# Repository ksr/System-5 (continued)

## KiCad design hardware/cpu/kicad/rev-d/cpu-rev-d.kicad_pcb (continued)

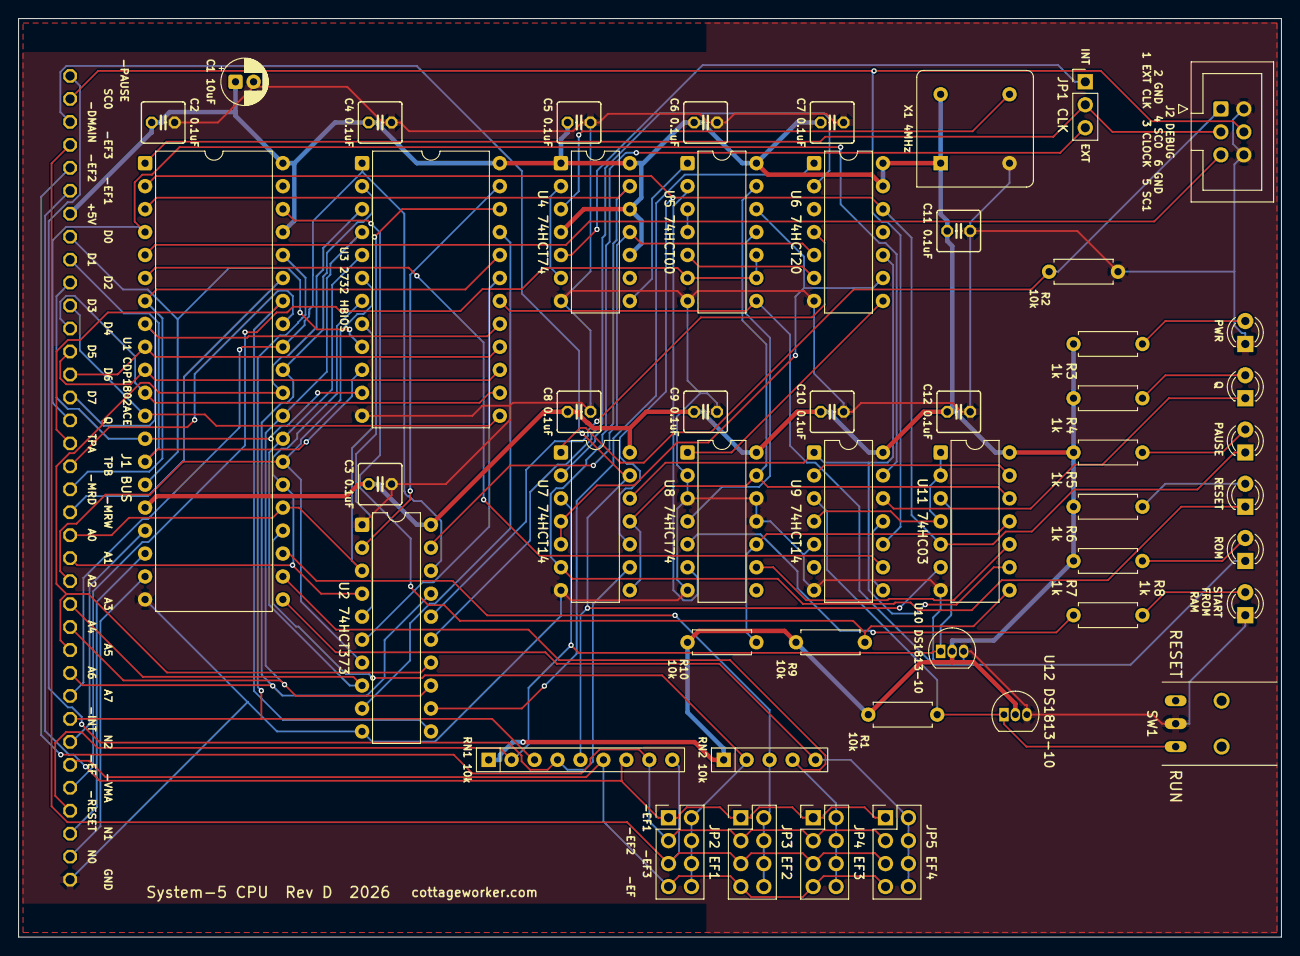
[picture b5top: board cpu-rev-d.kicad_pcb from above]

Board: 2 copper layers, 139.7 x 101.6 mm, 51 parts (0 on the bottom side), 83 nets.

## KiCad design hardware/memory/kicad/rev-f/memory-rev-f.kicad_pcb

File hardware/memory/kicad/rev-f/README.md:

# Memory Rev F (MEM3-F): KiCad master

> **Rev F (2026-11-18) is Rev E with EEPROM sockets and its silkscreen fixed.** Ken asked that morning for "the next
> version of memory card with fixed silkscreen", and that evening "yes put in Rev F but that isnt being ordered today"
> for the EEPROM sockets of `BACKLOG.md` (2026-10-30). Each EPROM socket takes a 27C256, as before, or a 28C256 EEPROM
> that the 1802 can rewrite in place. A jumper block per socket picks which (below).
>
> **Copper:** Rev E's, except where the sockets changed. 1,078 of Rev E's 1,084 track segments and vias are kept,
> identical and locked. The 6 that carried A14 through IC3's and IC5's pin 27 are gone. Freerouting added 74 segments
> and 1 via for the new connections, and a 75th, a 0.05 mm stitch inside one of Rev E's tracks (IC4's D6 net). Both planes,
> and every part but the four new ones, are where Rev E has them. Rev E (`../rev-e/README.md`) has been the card in
> the machine since 2026-10-31; its notes on building it (74HCT151 for all four muxes, the CD4050B buffers) apply to
> Rev F unchanged.
>
> **Not ordered** (Ken: not today). Before an order: `~/Developer/pcb-check/pcb-check
> hardware/memory/kicad/rev-f/memory-rev-f.kicad_pcb hardware/memory/kicad/rev-f/memory-rev-f-gerbers.zip --layers 4
> --tests` (Ken's check for every system), then Ken's look at the pictures and the fab's viewer. It is a **4-layer**
> board, as Rev E (In1 GND, In2 VCC).

## The EEPROM sockets

A 27C256 and a 28C256 have the same pins but two of them do other jobs:

| Socket pin | 27C256 (EPROM) | 28C256 (EEPROM) | Rev E |
|---|---|---|---|
| 1 | VPP: must be at VCC to read | A14 | tied to VCC |
| 27 | A14 | !WE, the write strobe | on A14 (BUFFADDR14, the CD4042B's latched A14) |

So a 28C256 in Rev E reads only its top 16K, and it takes a write whenever the CPU writes to one of its blocks with
A14 low. Rev F gives each socket's pins 1 and 27 to a 2 x 3 jumper block: **JP1 for IC5** (EPROM HI) and **JP2 for
IC3** (EPROM LO), at the top edge beyond the card guide (the layout rules: jumper blocks at an edge).

| JP pin | | JP pin | |
|---|---|---|---|
| 1 | VCC | 2 | A14 |
| 3 | the socket's pin 1 | 4 | the socket's pin 27 |
| 5 | A14 | 6 | WR, the RAMs' write strobe (-MWR through IC8, a CD4050B) |

**R6 (IC5) and R7 (IC3), 47k from pin 27 to VCC**, stand upright beside the blocks. With no shunt on 4-6 they hold a
28C256's !WE high, so it cannot be written.

### Settings

With the card standing in the bus, each block's right-hand column (pins 1, 3, 5) sets the socket's pin 1, and the
left-hand one (pins 2, 4, 6) its pin 27. The silkscreen says `27C256` at the lower end and `WRITE  28C256` at the
upper end, each word over its column.

| In the socket | Shunts | Pin 1 | Pin 27 |
|---|---|---|---|
| **27C256** (as Rev E; the default) | **1-3 and 2-4**: both at the `27C256` end | VCC (VPP) | A14 |
| **28C256, read-only** | **3-5** only: the right-hand column, at the `28C256` end | A14 | !WE held high by R6 / R7 |
| **28C256 the CPU can write** | **3-5 and 4-6**: both at the `WRITE  28C256` end | A14 | !WE on WR |

- **Never put A14 on a 27C256's pin 1** (3-5 with a 27C256): VPP low is Rev B's misread fault.
- **With a 28C256, keep 2-4 empty.** It would put !WE on A14, so a write to one of the chip's blocks with A14 low
  would change the ROM. In the read-only setting, store the spare shunt off the block or on one pin only.
- **Never fit a shunt across a row** (1-2, 3-4, 5-6). 1-2 ties A14 to VCC, 5-6 ties it to WR, and 3-4 joins pins 1
  and 27.
- The read-only setting is the one to keep. Fit 4-6 only while the 1802 rewrites the chip.
- **Writing a 28C256:** each byte (or page of up to 64 bytes) starts an internal write of up to 10 ms. Until it ends,
  a read of the chip returns bit 7 of the byte written inverted ("data polling"), so software must poll or wait before
  the next write. Some 28C256s come with software data protection on; they then take a write only after the data
  sheet's unlock sequence. The emulator lands a write at once and models neither the wait nor the protection.

### Choices behind it

- **47k, not 10k.** With a 27C256 the shunt on 2-4 puts the pull-up on A14, which a CD4042B output drives. A CD4042B
  is rated for about 0.5 mA at a valid low (the reason Rev D/E need 74HCT151 muxes: `../rev-e/README.md`). Two 10k
  pull-ups would draw 0.9 mA, two 47k draw 0.2 mA. A 28C256's !WE input leaks at most 10 uA, which is 0.5 V across 47k.
- **Upright resistors** (KiCad's `R_Axial_DIN0207_L6.3mm_D2.5mm_P2.54mm_Vertical`). A lying 0207 put R6 between JP1
  and R5 with no room for its label: it landed in JP2's legend. Upright, each label sits right under its resistor.
- **WR, not a new gate.** The EEPROM's !WE is the RAMs' write strobe. A write reaches the chip only while its !CE is
  low, so only in its own blocks.
- **Timing** (`python3 -m s5emu.timing --cpu D 2`, from the netlists, with the AT28C256-15's limits typed in from
  memory, to verify against the data sheet): at 2 MHz the write pulse is at least 815 ns long (100 ns needed). The
  data is set up 2255 ns more than the 50 ns needed, and the address and !CE settle 1015 ns before !WE falls. At
  1.76 MHz the margins are larger. A 28C256-15 reads in 150 ns, faster than the 27C256-20's 200 ns.
- **Boot:** HBIOS (v1.0.4 and v1.0.8) and Elf/OS v5 never write 8000-EFFF. Elf/OS's memory probe (`f_freemem`) stops
  below 7800, so even the writable setting keeps its ROM through a boot (checked in the emulator, below).

## What changed from Rev E: the silkscreen

Two of Ken's rules for new boards decide it: every label readable with the parts fitted, outside each part (Ken,
2026-10-31, after MEM3-E), and **all silkscreen text upright, left to right, with the card standing in the bus,
connector down** (Ken, 2026-11-18, every board on every system; MEM3-E is the rule's own example of the problem, "drawn
to be read lying flat": 77 texts at 0, 30 at 90, 4 at 180, only the 5 LED labels at 270). System-5's cards are drawn
with the bus on the left, so on Rev F **every text is at KiCad angle 270**, except the name line, which the rule lets
run up a side edge.

| | Rev E | Rev F |
|---|---|---|
| Chip labels | name, type and job in the middle of each chip's outline, **under the chip** once it is in its socket (IC2's was hidden in bring-up), at 0 | at one end of each chip, clear of its pins: `IC7 CD4050` over `A0-A5 BUFFER`, the types as the parts list has them (CD4050, not 4050); where two lines have no room, one (`IC2 74HCT151  RAM LO 4K SEL`) or the name and type alone (IC13, IC15, IC4: `IC13 74HCT151`; their jobs are in the schematic). IC3 and IC5 read `27C256/28C256`. The bottom row's four (IC7, IC8, IC9, IC6) are at 0.8 mm: they share the 6.2 mm between their pins and J1's with the bus pins' names |
| Bus connector | Eagle's `U$1`, unlabelled; its pins' names at 0, on the board side of the pads | **J1** (the schematic too); the 30 pins' names at 270 in two staggered rows (one row would not fit the 2.54 mm pitch), **on the board side of the pads**, as Rev E has them; `J1 BUS` in the margin past the header's GND end. The footprint draws the part now: a single-row right-angle pin header whose plastic body lies between the pads and the card edge (below) |
| Capacitors, resistors, networks | `C4 0.1uF` at 90 or 0 | the same, at 270, beside each; the networks' pin 1 marked; R6 and R7 on two lines under each |
| Jumper blocks | addresses at 90, ROM / GND / RAM and `HI 32K` / `LO 32K` at 0 | all at 270: each 4K block's address beside its row of pins, the three rows named under them (staggered as the bus pins), the blocks' names beyond the addresses, SV1-SV4 named; JP1 `EPROM HI` and JP2 `EPROM LO` with their `27C256` / `WRITE  28C256` legends |
| LEDs | `EPROM HI` ... `PWR` at 270 | as Rev E (the only labels that were right); `pcb-check.ini` exempts their references, as on CPU Rev D and the IO panel. `RAM HI` alone stands 0.5 mm further from R3 since 2026-11-19: Rev E has R3 1.27 mm nearer the front edge than the other LEDs' resistors, and the label's end came within 0.1 mm of the resistor's drawing (`pcb-check`, once its LABELS line read every text: "'RAM HI' under R3"; it was not hidden) |
| Name | `MEM3-E   System-5 64K RAM/EPROM   2026` | `System-5 memory  Rev F  2026` (1.2 mm; Ken, the evening of 2026-11-18: one naming for every card, no code like MEM3-F; `pcb-check.ini`'s name with it) with `cottageworker.com` (1.0 mm) right after it (Ken, 2026-10-26), along the bottom edge as drawn: up the right-hand side with the card standing. It starts where the bottom card-guide strip ends (3.00 in from the bus edge): no label is in either strip |
| Courtyards and bodies | none (the footprints came from Eagle: a silkscreen outline and pads) | a courtyard round each part's pads, 0.1 mm out, in the board and in this folder's copy of the footprint library; J1's round the header's body too. Since 2026-11-19 each chip footprint (DIL14, DIL16, DIL28, DIL28-6) also has a **body on F.Fab, the chip in its socket**: 1.33 mm past the end pins and 1.27 mm past the rows, as KiCad draws its DIP sockets |

The footprints' own texts (the old bus-pin names and passives' labels, which KiCad keeps no hidden flag for) are on
F.Fab now, off the silkscreen.

**The bus pins' names were under the header, and are not now (the night of 2026-11-18).** As first drawn that day, Rev
F had the thirty names and `J1 BUS` in the strip between J1's pads and the card edge. J1 is a right-angle pin header,
and its plastic body lies in that strip, 1.5 to 4.0 mm from the pads (the photo of the built MEM3-E shows it,
`../rev-e/photos/`): on a built card all thirty would have been hidden. Nothing caught it, because the C30 footprint
drew pads and no part, so the label placer and `pcb-check` took the strip for free board (found on VIDEO-G, where
`J1 BUS` had the same fault; `hardware/video-g/kicad/README.md`). Now this folder's `C30` draws the header: its body on
F.Fab, a courtyard round body and pads, and KiCad's 3D model, so the render shows the connector. `gen/silk.py` brings
the board's J1 up to it (`tools/kicad/fp_update.py`) and places the names on the board side, 1.84 and 3.51 mm from the
pads, with the bottom row's chip labels beside them. Silkscreen only: the copper is the same, track for track.

**The chips' bodies drawn (2026-11-19).** `pcb-check` got a line for this fault, BODIES: a warning for each part with
nothing drawn on the fab layer, since the checks cannot see such a part. Rev F's fourteen chips were of that kind
(Eagle's footprints: pads and a silkscreen outline between the rows). Each has its socket's frame on F.Fab now, and the
placer keeps labels off it: `IC12` and `IC14`'s labels had stood 0.2 mm inside the frame's end and moved 0.4 mm out;
`IC1`, `IC11` and `IC2`'s moved 0.2 mm; `C8 10uF` is under its capacitor again, at 0.8 mm. Nothing else moved, and the
copper is the same, track for track. The same day BODIES learned to name a fab-layer drawing far smaller than the
part's courtyard, a mark and not a body, and Eagle's other footprints here were of that kind: the bypass capacitors
(two lead stubs), the pin headers (their pins), the resistor networks, the resistors, C8 and the LEDs. Each has its
body on F.Fab now, as its silkscreen outline draws it (the capacitors as on the other new cards, 4.0 x 2.5 mm); no
label moved for it. The courtyards stay round the pads alone: Rev E's parts stand closer than their bodies' outlines
would allow courtyards to.

## How it is made

`gen/build.sh` (KiCad 10, Freerouting 1.9) builds and checks it all, from Rev E's files each run:

1. `gen/make_schematic.py`: Rev E's schematic with J1, the new title block and the EEPROM sockets (IC3 / IC5 pins 1
   and 27 on the jumper blocks, JP1, JP2, R6, R7 and a note). Then ERC, the netlist, the parts list
   (`memory-rev-f-bom.csv`) and the schematic PDF.
2. `gen/make_board.py`: Rev E's board with U$1 renamed J1, IC3 / IC5 pins 1 and 27 on their new nets, the A14 copper
   at pin 27 removed, the four new parts placed, every remaining track locked.
3. `gen/route.py dsn`, Freerouting, `gen/route.py import`: the new connections only, on F.Cu / B.Cu (the planes stay
   power layers), in a fixed order (`ROUTE_SEED` 1: seeds 0 and 3 leave JP2's A14 unrouted).
4. `gen/silk.py`: brings the drawing of every part from this folder's library up to its file (J1's header body,
   courtyard and 3D model; the chips' bodies in their sockets; the courtyards), removes
   Rev E's silkscreen texts (keeping the LEDs'), moves the footprints' own texts to F.Fab, adds the courtyards, and
   writes every label again at 270, each at the first spot clear of every pad (0.3 mm), part body, outline, courtyard
   and other text.
5. DRC with schematic parity, the order files, and `tools/preorder_check.py --layers 4`, which also redraws
   `schematic/` (from `spec.py`) and rebuilds the book.

## Checks (2026-11-18)

- `tools/preorder_check.py --layers 4`: **PASS**: ERC 0 errors (Rev E's 6 warnings), DRC 0 errors (311 silkscreen
  notes), 0 unconnected, schematic parity 0, the netlist proof 92 of 92, the planes (57 GND and 45 VCC pads reach
  them), the zip fresh and complete, the redrawn schematic matched.
- `pcb-check --layers 4 --tests` at elf `644a51a`: **no failures, 0 warnings** (the five LEDs labelled by function,
  as `pcb-check.ini` allows). LABELS, DESIGN (no input floating, no output fight), FOOTPRINTS and COPPER (rebuilt from
  the gerbers: no shorts or opens) pass with the new parts. **That pass was with the bus pins' names under the header**
  (above): pcb-check could not know the header's body, which the footprint did not draw. The board as it is now, with
  the names on the board side and the body in the footprint, passes `tools/preorder_check.py --layers 4` again (the
  same counts; the copper is the same track for track) and **`pcb-check --layers 4 --tests` at elf `d1df002`
  (2026-11-19, pcb-check `71c4bef`): no failures, 0 warnings**; LABELS: every reference and value on the silk, clear of
  the parts, the header's body among them now. **Again at elf `b4692e9`** with the chips' bodies drawn (pcb-check
  `bd032dd`, which has the BODIES line) and at **`b2252b7`** with every Eagle footprint's (pcb-check `0b45f65`, whose
  BODIES also names a mark that is not a body): **no failures, 0 warnings** each time; BODIES: every part drawn with
  its body. pcb-check `1525f36`, whose LABELS line reads every silkscreen text, then gave one warning at `4e2dff4`,
  "'RAM HI' under R3" (the table above); with that label 0.5 mm further from R3, at elf **`bb0b711`**: **no failures,
  0 warnings**, every text clear of the parts.
- The emulator (`software/s5emu`) runs Rev F's netlist with the shunts as netlist edits:
  - `--hw --mem-rev F`: a 27C256 in each socket, JP1 and JP2 at 1-3 and 2-4.
    `tests/test_hw.Decode.test_rev_f_is_rev_d` checks that it decodes, writes and reads as Rev D, the card of record,
    for every 4K block as RAM, EPROM or neither, down to the address inside each chip. Without the 2-4 shunts, R6 /
    R7 would hold the EPROM's A14 high. `Boot.test_rev_f_boots_clean` boots HBIOS.
  - `--mem-rev F-28C256` (JP1 3-5) and `F-28C256-W` (3-5 and 4-6): a 28C256 in IC5 (`Netlist.refit`: pin 1 A14,
    pin 27 !WE). `Decode.test_rev_f_28c256_in_ic5` checks that it reads as the 27C256 did. Read-only, it takes no
    write. Writable, the CPU writes it at the address it reads, and a RAM write reaches only the RAM.
  - `SystemV5`: the whole machine from its netlists (CPU Rev D, the IO panel, Rev F with the writable 28C256) boots
    Elf/OS v5 on HBIOS v1.0.8 and leaves the EEPROM untouched.
  - `tests/test_timing.RevDAt2MHz.test_memory_rev_f_28c256_write`: the write timing above.

## Files

| File | |
|---|---|
| `memory-rev-f.kicad_pcb` / `.kicad_sch` / `-sheet1.kicad_sch` / `.kicad_pro` | the KiCad master |
| `memory-rev-f-gerbers.zip`, `gerbers/` | the order files (4 copper layers; PTH and NPTH drills) |
| `memory-rev-f-schematic.pdf`, `schematic/memory-rev-f-schematic.pdf` | the KiCad schematic; the redrawn one |
| `memory-rev-f-placement.pdf`, `memory-rev-f-render-top.png`, `check-memory-rev-f-*.png` | placement, render, each copper layer read back from the zip |
| `memory-rev-f-bom.csv` | the parts list: Rev E's, with J1, JP1, JP2 and R6 / R7 (47k, upright); add four 2.54 mm shunts |
| `gen/` | `build.sh` and the scripts it runs (above) |
| `pcb-check.ini` | pcb-check's settings: name and rev, the bus edge, the tests, the LEDs' exemption |

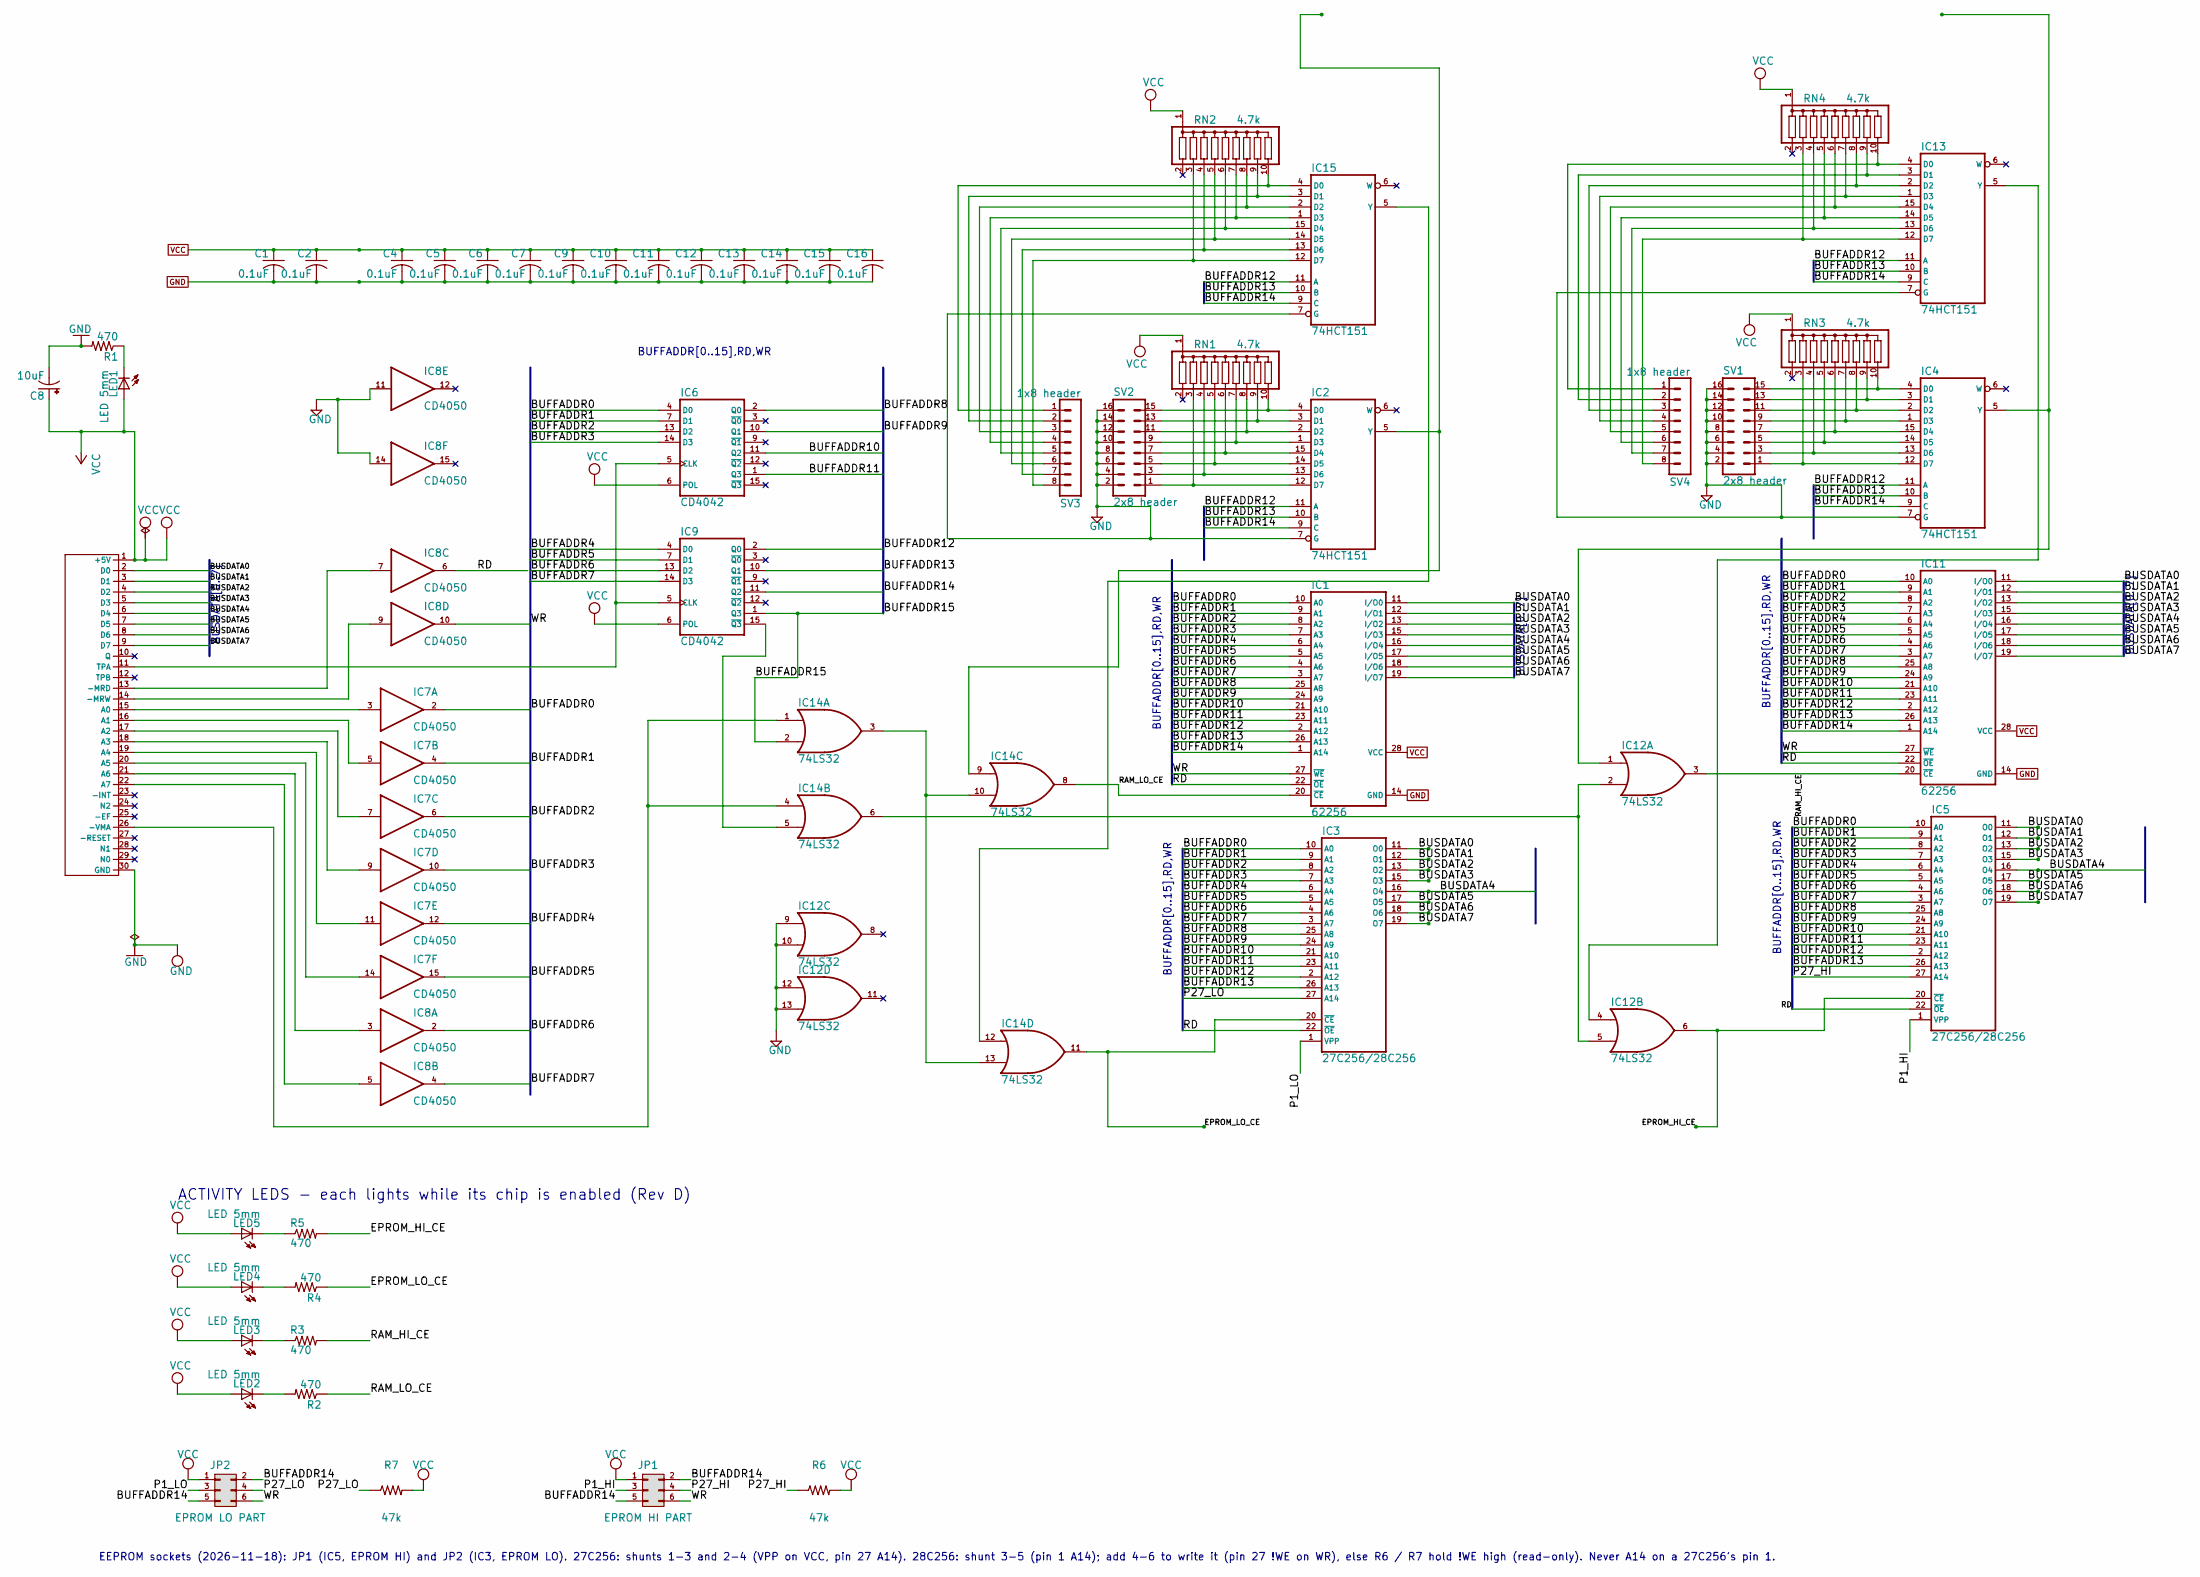
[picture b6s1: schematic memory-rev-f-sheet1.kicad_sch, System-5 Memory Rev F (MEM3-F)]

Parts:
C1, C2, C4, C5, C6, C7, C9, C10, C11, C12, C13, C14, C15, C16: 0.1uF; C025-050X050
C8: 10uF; E2,5-7
IC1, IC11: 62256; DIL28-6
IC2, IC4, IC13, IC15: 74HCT151; DIL16
IC3, IC5: 27C256/28C256; DIL28
IC6, IC9: CD4042; DIL16
IC7, IC8: CD4050; DIL16
IC12, IC14: 74LS32; DIL14
J1: System-5 bus 30-pin; C30
JP1: EPROM HI PART; PinHeader_2x03_P2.54mm_Vertical
JP2: EPROM LO PART; PinHeader_2x03_P2.54mm_Vertical
LED1, LED2, LED3, LED4, LED5: LED 5mm; LED5MM
R1, R2, R3, R4, R5: 470; 0207_7
R6, R7: 47k; R_Axial_DIN0207_L6.3mm_D2.5mm_P2.54mm_Vertical
RN1, RN2, RN3, RN4: 4.7k; SIL10
SV1, SV2: 2x8 header; MA08-2
SV3, SV4: 1x8 header; MA08-1

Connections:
/Sheet 1/BUFFADDR0: IC1.10 (A0), IC3.10 (A0), IC5.10 (A0), IC6.4 (D0), IC7.2 (O), IC11.10 (A0)
/Sheet 1/BUFFADDR1: IC1.9 (A1), IC3.9 (A1), IC5.9 (A1), IC6.7 (D1), IC7.4 (O), IC11.9 (A1)
/Sheet 1/BUFFADDR2: IC1.8 (A2), IC3.8 (A2), IC5.8 (A2), IC6.13 (D2), IC7.6 (O), IC11.8 (A2)
/Sheet 1/BUFFADDR3: IC1.7 (A3), IC3.7 (A3), IC5.7 (A3), IC6.14 (D3), IC7.10 (O), IC11.7 (A3)
/Sheet 1/BUFFADDR4: IC1.6 (A4), IC3.6 (A4), IC5.6 (A4), IC7.12 (O), IC9.4 (D0), IC11.6 (A4)
/Sheet 1/BUFFADDR5: IC1.5 (A5), IC3.5 (A5), IC5.5 (A5), IC7.15 (O), IC9.7 (D1), IC11.5 (A5)
/Sheet 1/BUFFADDR6: IC1.4 (A6), IC3.4 (A6), IC5.4 (A6), IC8.2 (O), IC9.13 (D2), IC11.4 (A6)
/Sheet 1/BUFFADDR7: IC1.3 (A7), IC3.3 (A7), IC5.3 (A7), IC8.4 (O), IC9.14 (D3), IC11.3 (A7)
/Sheet 1/BUFFADDR8: IC1.25 (A8), IC3.25 (A8), IC5.25 (A8), IC6.2 (Q0), IC11.25 (A8)
/Sheet 1/BUFFADDR9: IC1.24 (A9), IC3.24 (A9), IC5.24 (A9), IC6.10 (Q1), IC11.24 (A9)
/Sheet 1/BUFFADDR10: IC1.21 (A10), IC3.21 (A10), IC5.21 (A10), IC6.11 (Q2), IC11.21 (A10)
/Sheet 1/BUFFADDR11: IC1.23 (A11), IC3.23 (A11), IC5.23 (A11), IC6.1 (Q3), IC11.23 (A11)
/Sheet 1/BUFFADDR12: IC1.2 (A12), IC2.11 (A), IC3.2 (A12), IC4.11 (A), IC5.2 (A12), IC9.2 (Q0), IC11.2 (A12), IC13.11 (A), IC15.11 (A)
/Sheet 1/BUFFADDR13: IC1.26 (A13), IC2.10 (B), IC3.26 (A13), IC4.10 (B), IC5.26 (A13), IC9.10 (Q1), IC11.26 (A13), IC13.10 (B), IC15.10 (B)
/Sheet 1/BUFFADDR14: IC1.1 (A14), IC2.9 (C), IC4.9 (C), IC9.11 (Q2), IC11.1 (A14), IC13.9 (C), IC15.9 (C), JP1.2, JP1.5, JP2.2, JP2.5
/Sheet 1/BUFFADDR15: IC9.1 (Q3), IC14.2 (I1)
/Sheet 1/BUSDATA0: IC1.11 (I/O0), IC3.11 (O0), IC5.11 (O0), IC11.11 (I/O0), J1.2 (D0)
/Sheet 1/BUSDATA1: IC1.12 (I/O1), IC3.12 (O1), IC5.12 (O1), IC11.12 (I/O1), J1.3 (D1)
/Sheet 1/BUSDATA2: IC1.13 (I/O2), IC3.13 (O2), IC5.13 (O2), IC11.13 (I/O2), J1.4 (D2)
/Sheet 1/BUSDATA3: IC1.15 (I/O3), IC3.15 (O3), IC5.15 (O3), IC11.15 (I/O3), J1.5 (D3)
/Sheet 1/BUSDATA4: IC1.16 (I/O4), IC3.16 (O4), IC5.16 (O4), IC11.16 (I/O4), J1.6 (D4)
/Sheet 1/BUSDATA5: IC1.17 (I/O5), IC3.17 (O5), IC5.17 (O5), IC11.17 (I/O5), J1.7 (D5)
/Sheet 1/BUSDATA6: IC1.18 (I/O6), IC3.18 (O6), IC5.18 (O6), IC11.18 (I/O6), J1.8 (D6)
/Sheet 1/BUSDATA7: IC1.19 (I/O7), IC3.19 (O7), IC5.19 (O7), IC11.19 (I/O7), J1.9 (D7)
/Sheet 1/EPROM_HI_CE: IC5.20 (~CE), IC12.6 (O), R5.2
/Sheet 1/EPROM_LO_CE: IC3.20 (~CE), IC14.11 (O), R4.1
/Sheet 1/P1_HI: IC5.1 (VPP), JP1.3
/Sheet 1/P1_LO: IC3.1 (VPP), JP2.3
/Sheet 1/P27_HI: IC5.27 (A14), JP1.4, R6.1
/Sheet 1/P27_LO: IC3.27 (A14), JP2.4, R7.1
/Sheet 1/RAM_HI_CE: IC11.20 (~CE), IC12.3 (O), R3.2
/Sheet 1/RAM_LO_CE: IC1.20 (~CE), IC14.8 (O), R2.1
/Sheet 1/RD: IC1.22 (~OE), IC3.22 (~OE), IC5.22 (~OE), IC8.6 (O), IC11.22 (~OE)
/Sheet 1/WR: IC1.27 (~WE), IC8.10 (O), IC11.27 (~WE), JP1.6, JP2.6
GND: C1.2, C2.2, C4.2, C5.2, C6.2, C7.2, C8.-, C9.2, C10.2, C11.2, C12.2, C13.2, C14.2, C15.2, C16.2, IC1.14 (GND), IC2.7 (G), IC2.8 (GND), IC3.14 (GND), IC4.7 (G), IC4.8 (GND), IC5.14 (GND), IC6.8 (GND), IC7.8 (GND), IC8.8 (GND), IC8.11 (I), IC8.14 (I), IC9.8 (GND), IC11.14 (GND), IC12.7 (GND), IC12.9 (I0), IC12.10 (I1), IC12.12 (I0), IC12.13 (I1), IC13.7 (G), IC13.8 (GND), IC14.7 (GND), IC15.7 (G), IC15.8 (GND), J1.30 (GND), R1.2, SV1.2, SV1.4, SV1.6, SV1.8, SV1.10, SV1.12, SV1.14, SV1.16, SV2.2, SV2.4, SV2.6, SV2.8, SV2.10, SV2.12, SV2.14, SV2.16
unnamed: IC2.4 (D0), RN1.10, SV2.15
unnamed: IC2.3 (D1), RN1.9, SV2.13
unnamed: IC2.2 (D2), RN1.8, SV2.11
unnamed: IC2.1 (D3), RN1.7, SV2.9
unnamed: IC2.15 (D4), RN1.6, SV2.7
unnamed: IC2.14 (D5), RN1.5, SV2.5
unnamed: IC2.13 (D6), RN1.4, SV2.3
unnamed: IC2.12 (D7), RN1.3, SV2.1
unnamed: IC4.4 (D0), RN3.10, SV1.15
unnamed: IC4.3 (D1), RN3.9, SV1.13
unnamed: IC4.2 (D2), RN3.8, SV1.11
unnamed: IC4.1 (D3), RN3.7, SV1.9
unnamed: IC4.15 (D4), RN3.6, SV1.7
unnamed: IC4.14 (D5), RN3.5, SV1.5
unnamed: IC4.13 (D6), RN3.4, SV1.3
unnamed: IC4.12 (D7), RN3.3, SV1.1
unnamed: IC6.5 (CLK), IC9.5 (CLK), J1.11 (TPA)
unnamed: IC7.3 (I), J1.15 (A0)
unnamed: IC7.5 (I), J1.16 (A1)
unnamed: IC7.7 (I), J1.17 (A2)
unnamed: IC7.9 (I), J1.18 (A3)
unnamed: IC7.11 (I), J1.19 (A4)
unnamed: IC7.14 (I), J1.20 (A5)
unnamed: IC8.3 (I), J1.21 (A6)
unnamed: IC8.5 (I), J1.22 (A7)
unnamed: IC8.7 (I), J1.13 (-MRD)
unnamed: IC8.9 (I), J1.14 (-MRW)
unnamed: IC4.5 (Y), IC12.1 (I0)
unnamed: IC12.2 (I1), IC12.5 (I1), IC14.6 (O)
unnamed: IC12.4 (I0), IC13.5 (Y)
unnamed: IC13.4 (D0), RN4.10, SV4.1
unnamed: IC13.3 (D1), RN4.9, SV4.2
unnamed: IC13.2 (D2), RN4.8, SV4.3
unnamed: IC13.1 (D3), RN4.7, SV4.4
unnamed: IC13.15 (D4), RN4.6, SV4.5
unnamed: IC13.14 (D5), RN4.5, SV4.6
unnamed: IC13.13 (D6), RN4.4, SV4.7
unnamed: IC13.12 (D7), RN4.3, SV4.8
unnamed: IC14.1 (I0), IC14.4 (I0), J1.26 (-VMA)
unnamed: IC14.3 (O), IC14.10 (I1), IC14.13 (I1)
unnamed: IC9.15 (~Q3), IC14.5 (I1)
unnamed: IC2.5 (Y), IC14.9 (I0)
unnamed: IC14.12 (I0), IC15.5 (Y)
unnamed: IC15.4 (D0), RN2.10, SV3.1
unnamed: IC15.3 (D1), RN2.9, SV3.2
unnamed: IC15.2 (D2), RN2.8, SV3.3
unnamed: IC15.1 (D3), RN2.7, SV3.4
unnamed: IC15.15 (D4), RN2.6, SV3.5
unnamed: IC15.14 (D5), RN2.5, SV3.6
unnamed: IC15.13 (D6), RN2.4, SV3.7
unnamed: IC15.12 (D7), RN2.3, SV3.8
unnamed: LED1.K (C), R1.1
unnamed: LED2.K (C), R2.2
unnamed: LED3.K (C), R3.1
unnamed: LED4.K (C), R4.2
unnamed: LED5.K (C), R5.1
VCC: C1.1, C2.1, C4.1, C5.1, C6.1, C7.1, C8.+, C9.1, C10.1, C11.1, C12.1, C13.1, C14.1, C15.1, C16.1, IC1.28 (VCC), IC2.16 (VCC), IC3.28 (VCC), IC4.16 (VCC), IC5.28 (VCC), IC6.6 (POL), IC6.16 (VCC), IC7.1 (VCC), IC8.1 (VCC), IC9.6 (POL), IC9.16 (VCC), IC11.28 (VCC), IC12.14 (VCC), IC13.16 (VCC), IC14.14 (VCC), IC15.16 (VCC), J1.1 (+5V), JP1.1, JP2.1, LED1.A, LED2.A, LED3.A, LED4.A, LED5.A, R6.2, R7.2, RN1.1, RN2.1, RN3.1, RN4.1

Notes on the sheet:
BUFFADDR[0..15],RD,WR
BUSDATA[0..7]
ACTIVITY LEDS - each lights while its chip is enabled (Rev D)
EEPROM sockets (2026-11-18): JP1 (IC5, EPROM HI) and JP2 (IC3, EPROM LO). 27C256: shunts 1-3 and 2-4 (VPP on VCC, pin 27 A14). 28C256: shunt 3-5 (pin 1 A14); add 4-6 to write it (pin 27 !WE on WR), else R6 / R7 hold !WE high (read-only). Never A14 on a 27C256's pin 1.

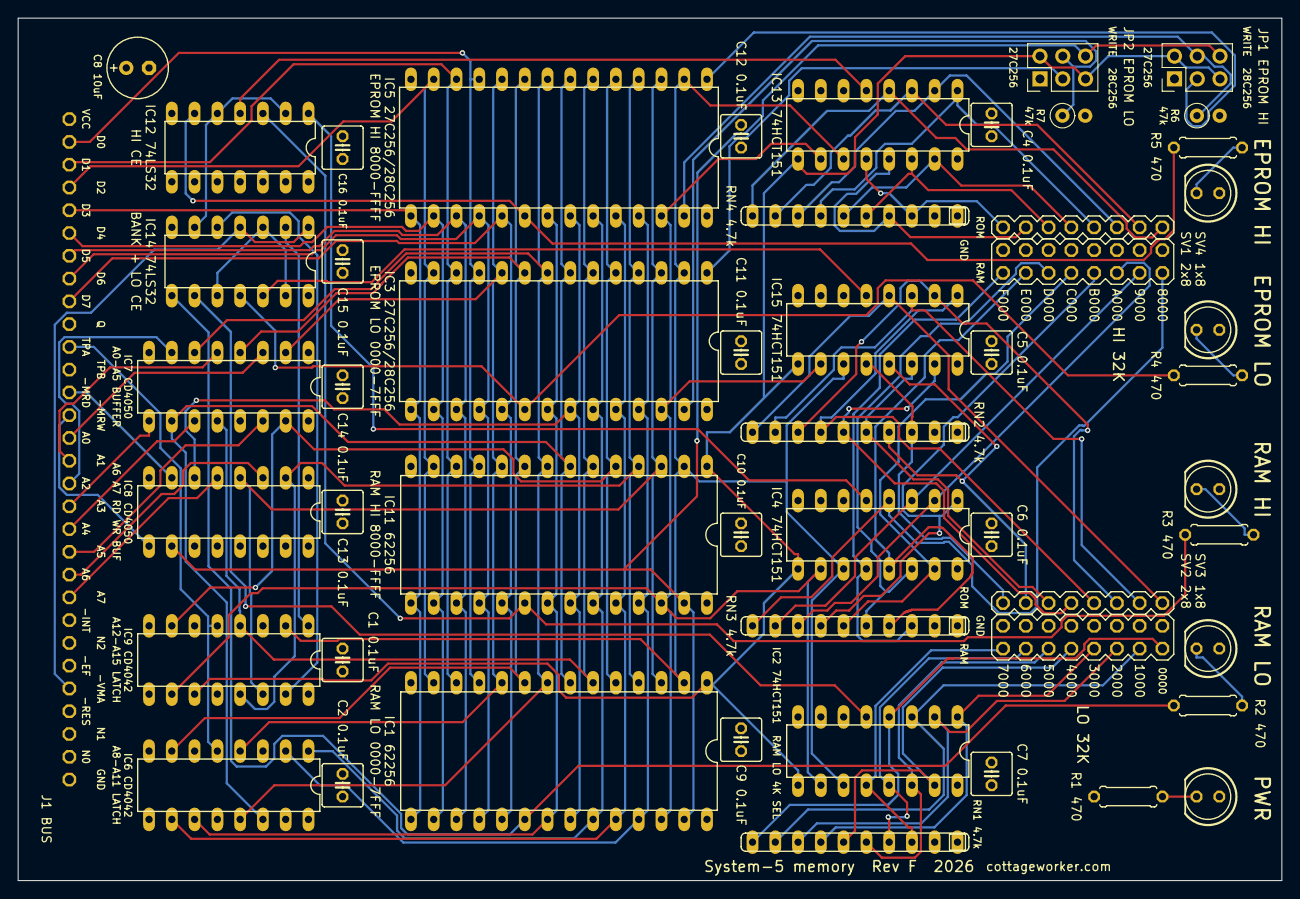
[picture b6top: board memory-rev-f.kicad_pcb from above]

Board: 4 copper layers, 140.9 x 96.2 mm, 52 parts (0 on the bottom side), 92 nets.

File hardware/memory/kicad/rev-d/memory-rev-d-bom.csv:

"Reference","Value","Footprint","QUANTITY"
"C1,C2,C4-C7,C9-C16","0.1uF","memory-rev-d-eagle:C025-050X050","14"
"C8","10uF","memory-rev-d-eagle:E2,5-7","1"
"IC1,IC11","62256","memory-rev-d-eagle:DIL28-6","2"
"IC2,IC4,IC13,IC15","74HCT151","memory-rev-d-eagle:DIL16","4"
"IC3,IC5","27256","memory-rev-d-eagle:DIL28","2"
"IC6,IC9","CD4042","memory-rev-d-eagle:DIL16","2"
"IC7,IC8","CD4050","memory-rev-d-eagle:DIL16","2"
"IC12,IC14","74LS32","memory-rev-d-eagle:DIL14","2"
"LED1-LED5","LED 5mm","memory-rev-d-eagle:LED5MM","5"
"R1-R5","470","memory-rev-d-eagle:0207_7","5"
"RN1-RN4","4.7k","memory-rev-d-eagle:SIL10","4"
"SV1,SV2","2x8 header","memory-rev-d-eagle:MA08-2","2"
"SV3,SV4","1x8 header","memory-rev-d-eagle:MA08-1","2"
"U$1","System-5 bus 30-pin","memory-rev-d-eagle:C30","1"
